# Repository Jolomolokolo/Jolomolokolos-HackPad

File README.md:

# RGB Keypad – Highway HackPad Project

This is my first ever HackPad for **"Highway"**, a project by Hack Club!

This project is a custom-built **4x4 mechanical keypad** featuring **MX switches**, per-key **RGB lighting** with **SK6812-E Mini LEDs**, and powered by a **Seeed XIAO RP2040** running **KMK firmware**. It's designed to be compact, programmable, and visually striking—perfect for learning firmware development and hardware design.

---

## Project Overview

### Hackpad Overview
This is an overview of the complete Hackpad project, including schematic, PCB, and layout:

---

### Schematic
The keypad uses a 4x4 matrix with 1N4148 diodes to prevent ghosting. The LEDs are chained together and controlled via GPIO10 on the RP2040.

---

### PCB Layout
Compact layout for both the keys and SK6812 LEDs. The board includes breakout pins for +5V, GND, and GPIO lines used in the matrix.

---

### Case & Assembly
The case is designed to fit tightly around the PCB, supporting the keys and exposing the RGB lighting. The XIAO is accessible from the back for flashing.

---

## Bill of Materials (BOM)

| Qty | Component                 | Description                            | Source |
|-----|---------------------------|----------------------------------------|-----------------------------|
| 1   | Seeed XIAO RP2040         | Microcontroller board                  | HC |
| 16  | Cherry MX Switch          | Mechanical keyboard switches           | HC |
| 16  | Blank DSA keycaps (White) | Keycaps for the switches               | HC |
| 16  | 1N4148 Diode              | For switch matrix                      | HC |
| 16  | SK6812-E Mini             | Individually addressable RGB LED       | JLCPCB |
| 4   | M3x16mm screws            | For mounting the case                  | HC |
| 4   | M3x5mx4mm heatset inserts | For mounting in case                   | HC |
| 1   | Custom PCB                | Designed in KiCad                      | JLCPCB |
| 1   | 3D-printed case           | PLA                                    | Self-printed |
| 1   | USB-C cable               | For power and programming              | Standard USB-C |

---

## Firmware

The firmware is written using [KMK Firmware](https://github.com/KMKfw/kmk_firmware), a powerful Python-based keyboard firmware.  
Each key is mapped in a 4x4 matrix and controls a matching RGB LED.  
See the `main.py` file for the implementation.

---

## Future Improvements

- Add layered key support
- Include OLED or rotary encoder
- Smoother Case

---

## License

This project is open-source under the MIT License.

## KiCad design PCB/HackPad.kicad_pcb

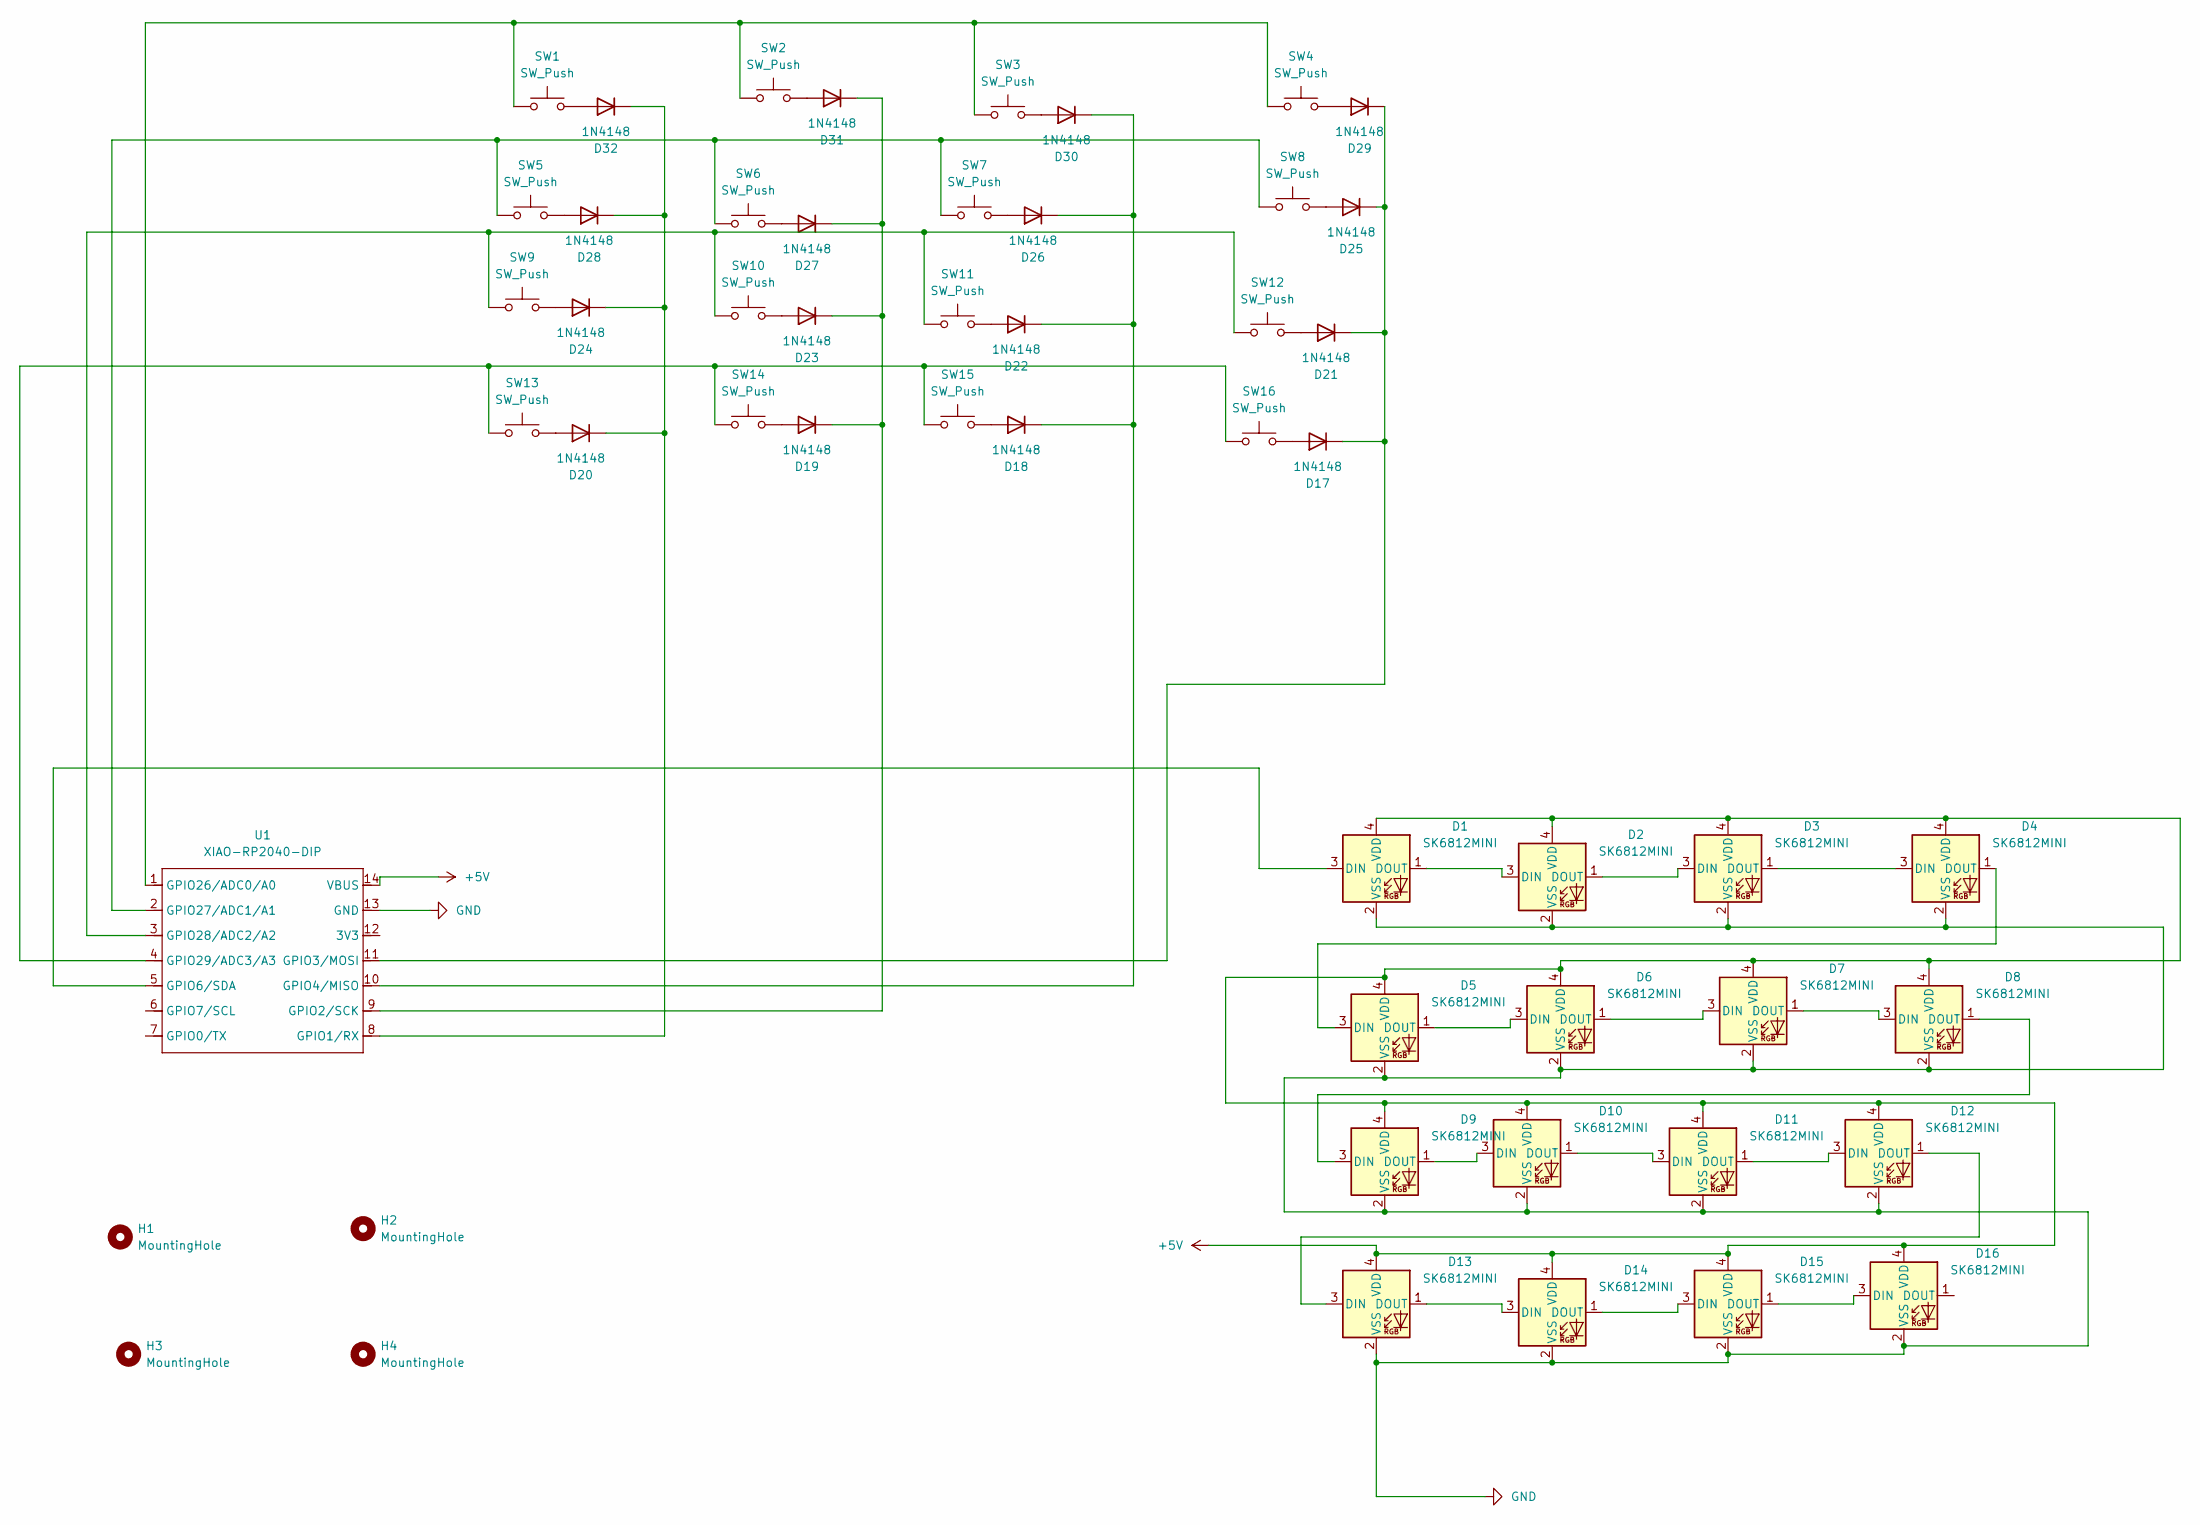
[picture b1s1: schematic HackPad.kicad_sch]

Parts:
D1, D2, D3, D4, D5, D6, D7, D8, D9, D10, D11, D12, D13, D14, D15, D16: SK6812MINI; SK6812-MINI-E
D17, D18, D19, D20, D21, D22, D23, D24, D25, D26, D27, D28, D29, D30, D31, D32: 1N4148; D_DO-35_SOD27_P7.62mm_Horizontal
H1, H2, H3, H4: MountingHole; MountingHole_3.5mm
SW1, SW2, SW3, SW4, SW5, SW6, SW7, SW8, SW9, SW10, SW11, SW12, SW13, SW14, SW15, SW16: SW_Push; SW_Cherry_MX_1.00u_PCB
U1: XIAO-RP2040-DIP

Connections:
+5V: D1.4 (VDD), D2.4 (VDD), D3.4 (VDD), D4.4 (VDD), D5.4 (VDD), D6.4 (VDD), D7.4 (VDD), D8.4 (VDD), D9.4 (VDD), D10.4 (VDD), D11.4 (VDD), D12.4 (VDD), D13.4 (VDD), D14.4 (VDD), D15.4 (VDD), D16.4 (VDD), U1.14 (VBUS)
GND: D1.2 (VSS), D2.2 (VSS), D3.2 (VSS), D4.2 (VSS), D5.2 (VSS), D6.2 (VSS), D7.2 (VSS), D8.2 (VSS), D9.2 (VSS), D10.2 (VSS), D11.2 (VSS), D12.2 (VSS), D13.2 (VSS), D14.2 (VSS), D15.2 (VSS), D16.2 (VSS), U1.13 (GND)
unnamed: D1.3 (DIN), U1.5 (GPIO6/SDA)
unnamed: D1.1 (DOUT), D2.3 (DIN)
unnamed: D2.1 (DOUT), D3.3 (DIN)
unnamed: D3.1 (DOUT), D4.3 (DIN)
unnamed: D4.1 (DOUT), D5.3 (DIN)
unnamed: D5.1 (DOUT), D6.3 (DIN)
unnamed: D6.1 (DOUT), D7.3 (DIN)
unnamed: D7.1 (DOUT), D8.3 (DIN)
unnamed: D8.1 (DOUT), D9.3 (DIN)
unnamed: D9.1 (DOUT), D10.3 (DIN)
unnamed: D10.1 (DOUT), D11.3 (DIN)
unnamed: D11.1 (DOUT), D12.3 (DIN)
unnamed: D12.1 (DOUT), D13.3 (DIN)
unnamed: D13.1 (DOUT), D14.3 (DIN)
unnamed: D14.1 (DOUT), D15.3 (DIN)
unnamed: D15.1 (DOUT), D16.3 (DIN)
unnamed: D17.2 (A), SW16.2
unnamed: D17.1 (K), D21.1 (K), D25.1 (K), D29.1 (K), U1.11 (GPIO3/MOSI)
unnamed: D18.2 (A), SW15.2
unnamed: D18.1 (K), D22.1 (K), D26.1 (K), D30.1 (K), U1.10 (GPIO4/MISO)
unnamed: D19.2 (A), SW14.2
unnamed: D19.1 (K), D23.1 (K), D27.1 (K), D31.1 (K), U1.9 (GPIO2/SCK)
unnamed: D20.2 (A), SW13.2
unnamed: D20.1 (K), D24.1 (K), D28.1 (K), D32.1 (K), U1.8 (GPIO1/RX)
unnamed: D21.2 (A), SW12.2
unnamed: D22.2 (A), SW11.2
unnamed: D23.2 (A), SW10.2
unnamed: D24.2 (A), SW9.2
unnamed: D25.2 (A), SW8.2
unnamed: D26.2 (A), SW7.2
unnamed: D27.2 (A), SW6.2
unnamed: D28.2 (A), SW5.2
unnamed: D29.2 (A), SW4.2
unnamed: D30.2 (A), SW3.2
unnamed: D31.2 (A), SW2.2
unnamed: D32.2 (A), SW1.2
unnamed: SW1.1, SW2.1, SW3.1, SW4.1, U1.1 (GPIO26/ADC0/A0)
unnamed: SW5.1, SW6.1, SW7.1, SW8.1, U1.2 (GPIO27/ADC1/A1)
unnamed: SW9.1, SW10.1, SW11.1, SW12.1, U1.3 (GPIO28/ADC2/A2)
unnamed: SW13.1, SW14.1, SW15.1, SW16.1, U1.4 (GPIO29/ADC3/A3)

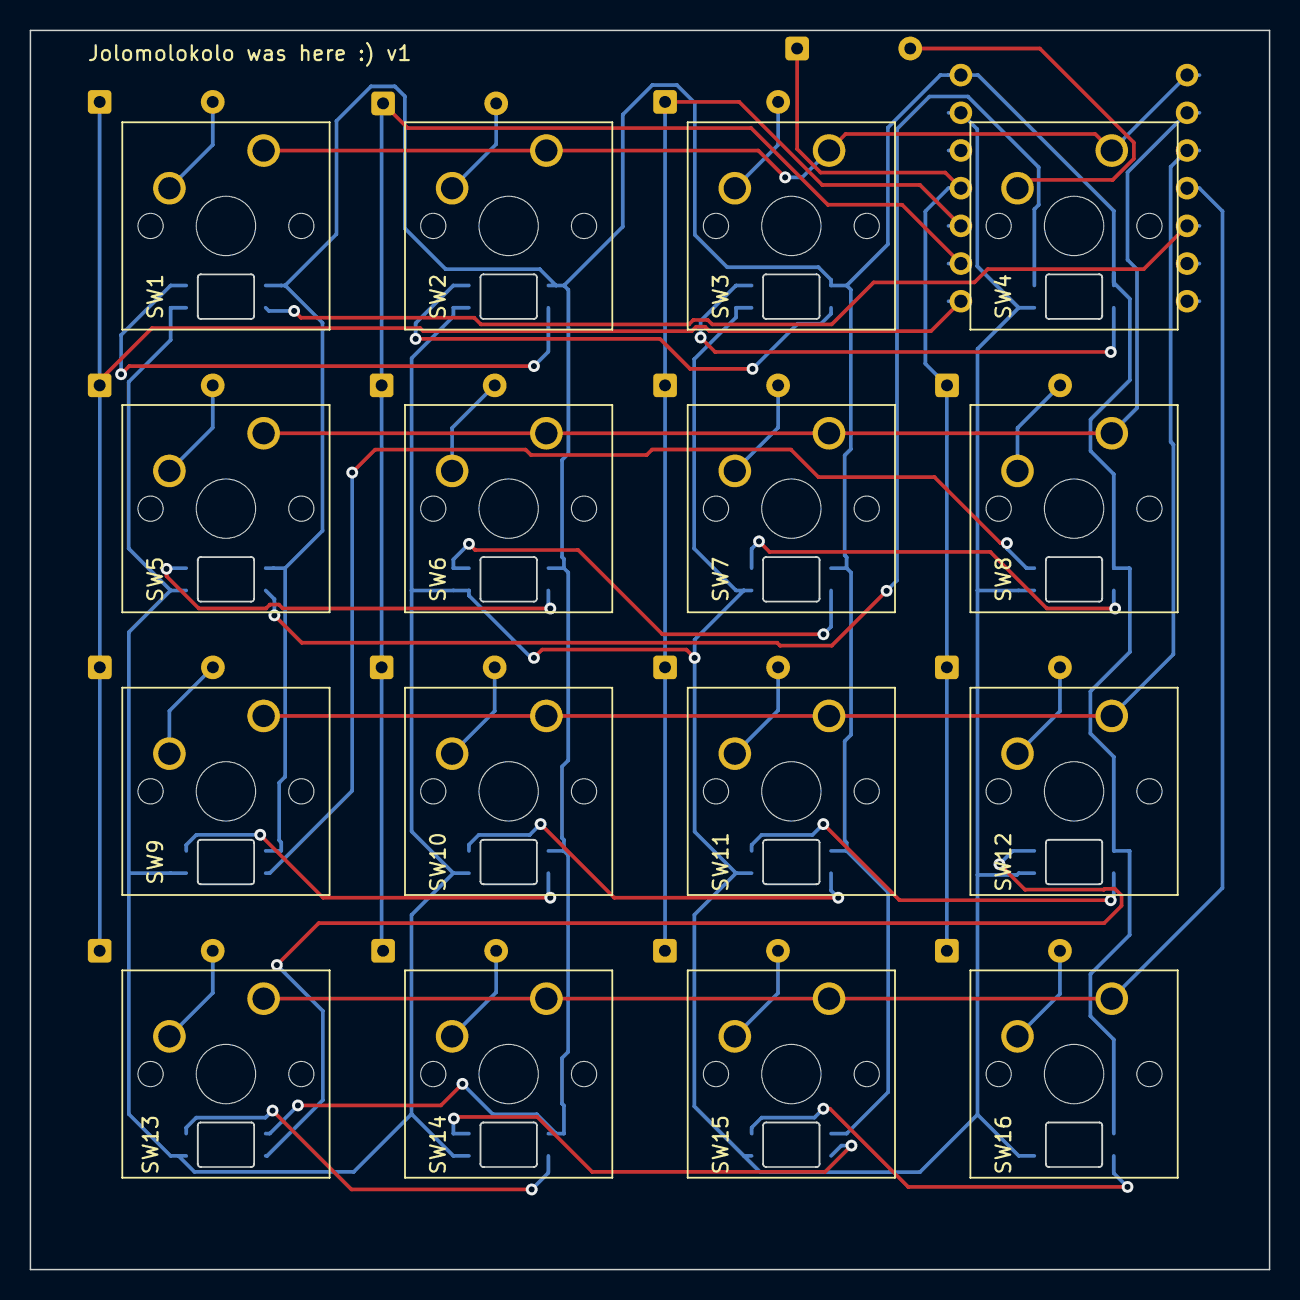
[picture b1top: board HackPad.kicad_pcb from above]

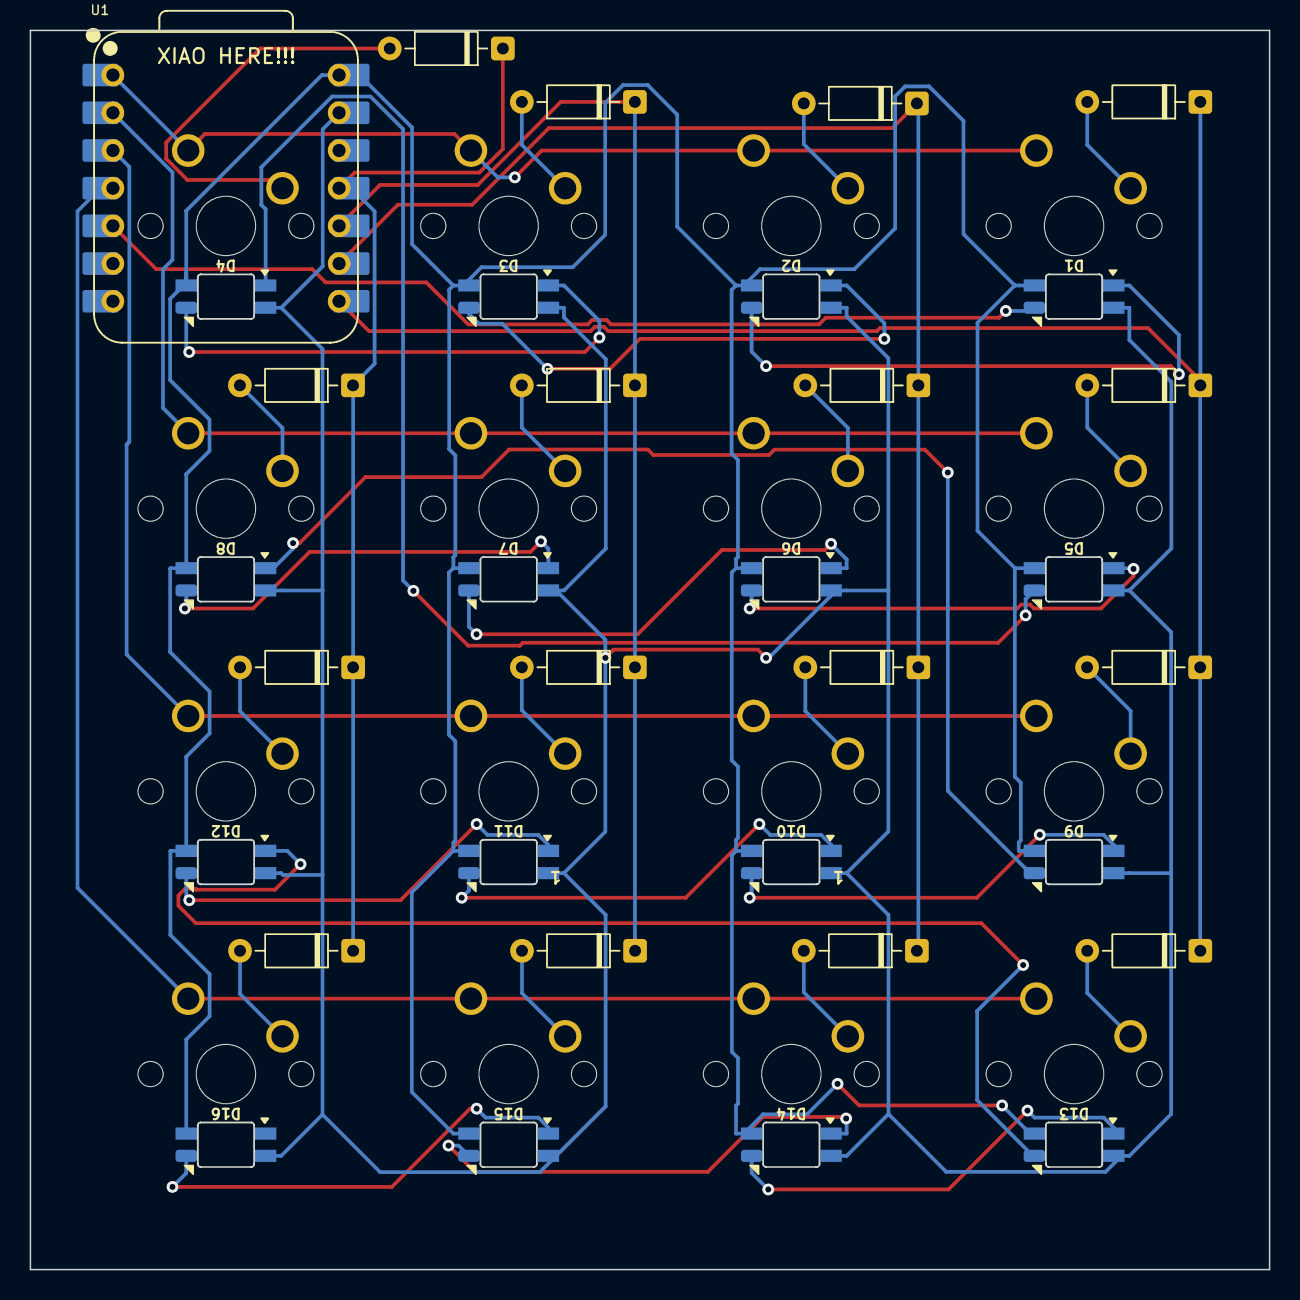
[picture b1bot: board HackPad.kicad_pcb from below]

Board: 2 copper layers, 83.5 x 83.5 mm, 49 parts (33 on the bottom side), 42 nets.

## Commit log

2025-06-22 README and Images for Release
2025-06-30 Added mounting holes for PCB
2025-06-30 Added .drl files
2025-06-30 Cleaned up and updated gerber files
2025-06-30 Create JOURNAL.md
    Started with journal, needs more informations and details!
